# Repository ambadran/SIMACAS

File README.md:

# SIMACAS - Smart Intillegent Monitoring and Control Agriculture System

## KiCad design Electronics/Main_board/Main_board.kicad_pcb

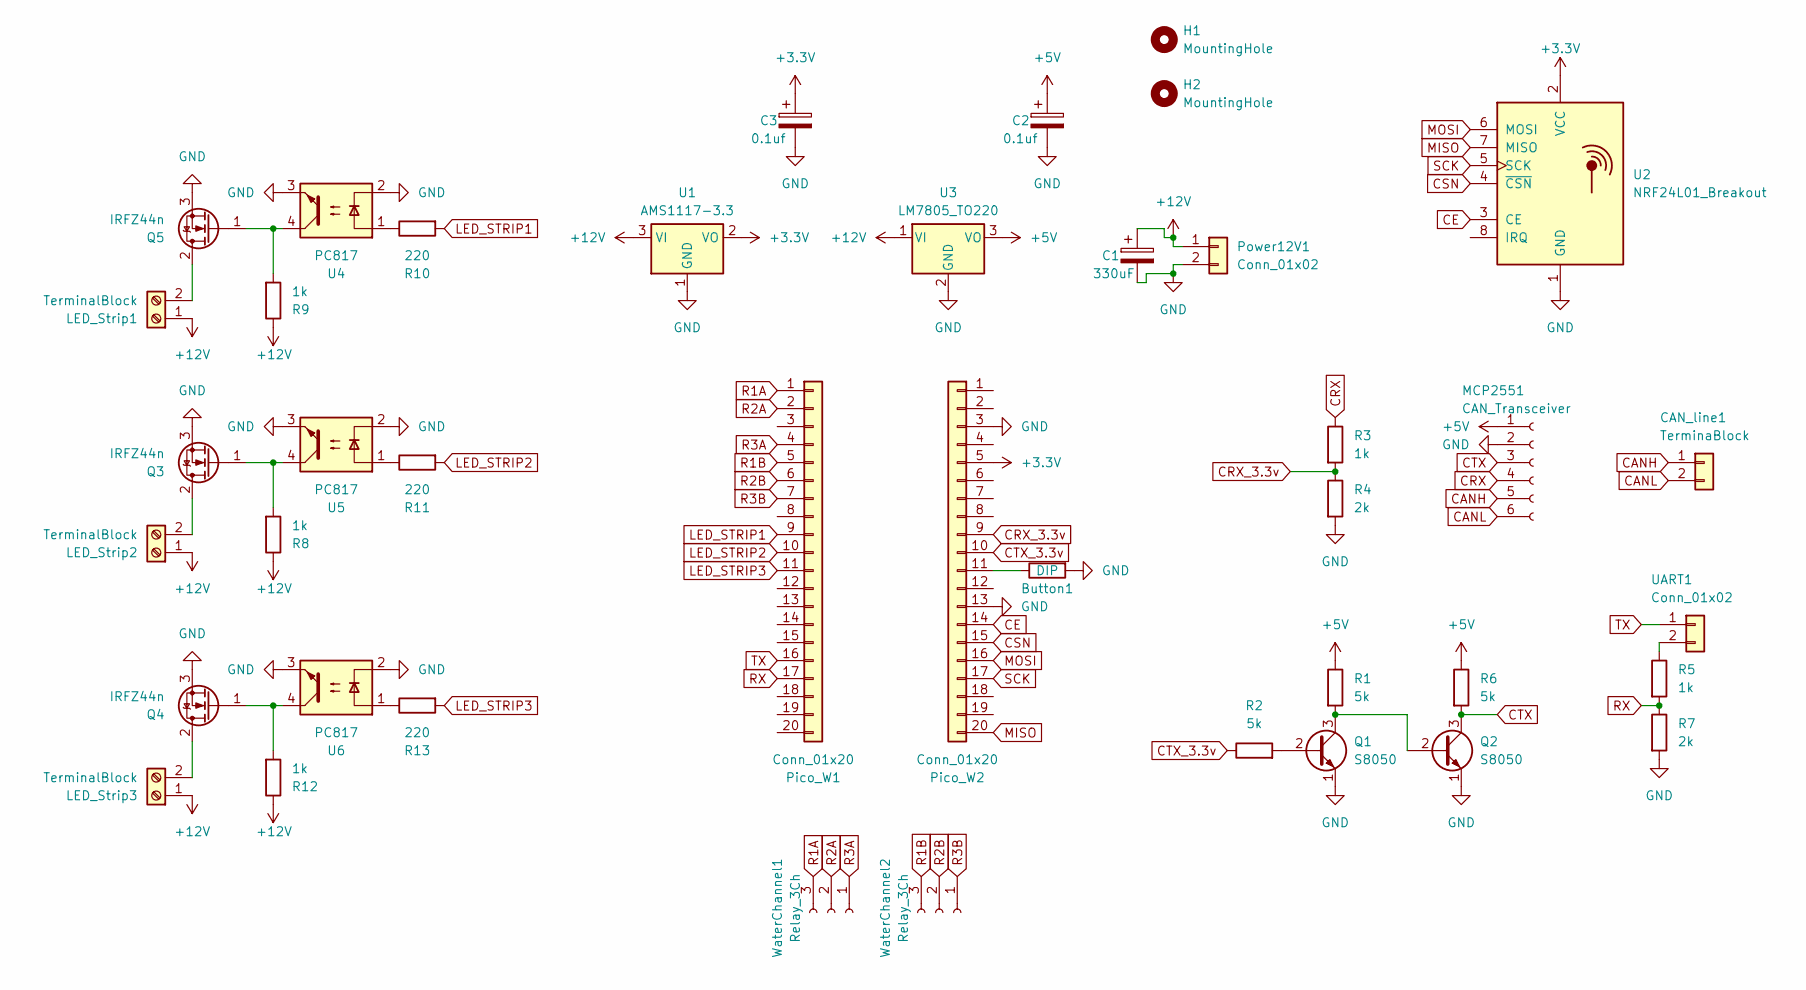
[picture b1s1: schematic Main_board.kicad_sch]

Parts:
Button1: DIP; R_Axial_DIN0207_L6.3mm_D2.5mm_P5.08mm_Vertical
C1: 330uF; CP_Radial_D8.0mm_P3.80mm
C2, C3: 0.1uf; CP_Radial_D4.0mm_P2.00mm
CAN_line1: TerminaBlock; TerminalBlock_bornier-2_P5.08mm
H1, H2: MountingHole; MountingHole_3.2mm_M3_DIN965_Pad_TopBottom
LED_Strip1, LED_Strip2, LED_Strip3: TerminalBlock; TerminalBlock_bornier-2_P5.08mm
MCP2551: CAN_Transceiver; PinSocket_1x06_P2.54mm_Vertical
Pico_W1, Pico_W2: Conn_01x20; PinSocket_1x20_P2.54mm_Vertical
Power12V1: Conn_01x02; JST_EH_B2B-EH-A_1x02_P2.50mm_Vertical
Q1, Q2: S8050; TO-92_Inline_Wide
Q3, Q4, Q5: IRFZ44n; TO-220-3_Vertical
R1, R2, R6: 5k; R_Axial_DIN0207_L6.3mm_D2.5mm_P7.62mm_Horizontal
R3, R5, R8, R9, R12: 1k; R_Axial_DIN0207_L6.3mm_D2.5mm_P7.62mm_Horizontal
R4, R7: 2k; R_Axial_DIN0207_L6.3mm_D2.5mm_P7.62mm_Horizontal
R10, R11, R13: 220; R_Axial_DIN0207_L6.3mm_D2.5mm_P7.62mm_Horizontal
U1: AMS1117-3.3; TO-220-3_Vertical
U2: NRF24L01_Breakout; nRF24L01_Breakout
U3: LM7805_TO220; TO-220-3_Vertical
U4, U5, U6: PC817; DIP-4_W7.62mm
UART1: Conn_01x02; JST_EH_B2B-EH-A_1x02_P2.50mm_Vertical
WaterChannel1, WaterChannel2: Relay_3Ch; JST_EH_B3B-EH-A_1x03_P2.50mm_Vertical

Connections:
+3.3V: C3.1, Pico_W2.5, U1.2 (VO), U2.2 (VCC)
+5V: C2.1, MCP2551.1, R1.1, R6.1, U3.3 (VO)
+12V: C1.1, LED_Strip1.1, LED_Strip2.1, LED_Strip3.1, Power12V1.1, R8.1, R9.1, R12.1, U1.3 (VI), U3.1 (VI)
CANH: CAN_line1.1, MCP2551.5
CANL: CAN_line1.2, MCP2551.6
CE: Pico_W2.14, U2.3 (CE)
CRX: MCP2551.4, R3.1
CRX_3.3v: Pico_W2.9, R3.2, R4.1
CSN: Pico_W2.15, U2.4 (~CSN)
CTX: MCP2551.3, Q2.3 (C), R6.2
CTX_3.3v: Pico_W2.10, R2.1
GND: Button1.2, C1.2, C2.2, C3.2, MCP2551.2, Pico_W2.3, Pico_W2.13, Power12V1.2, Q1.1 (E), Q2.1 (E), Q3.3 (S), Q4.3 (S), Q5.3 (S), R4.2, R7.2, U1.1 (GND), U2.1 (GND), U3.2 (GND), U4.2, U4.3, U5.2, U5.3, U6.2, U6.3
LED_STRIP1: Pico_W1.9, R10.2
LED_STRIP2: Pico_W1.10, R11.2
LED_STRIP3: Pico_W1.11, R13.2
MISO: Pico_W2.20, U2.7 (MISO)
MOSI: Pico_W2.16, U2.6 (MOSI)
unnamed: LED_Strip1.2, Q5.2 (D)
unnamed: LED_Strip2.2, Q3.2 (D)
unnamed: LED_Strip3.2, Q4.2 (D)
unnamed: Button1.1, Pico_W2.11
unnamed: Q1.2 (B), R2.2
unnamed: Q1.3 (C), Q2.2 (B), R1.2
unnamed: Q3.1 (G), R8.2, U5.4
unnamed: Q4.1 (G), R12.2, U6.4
unnamed: Q5.1 (G), R9.2, U4.4
unnamed: R10.1, U4.1
unnamed: R11.1, U5.1
unnamed: R13.1, U6.1
unnamed: R5.1, UART1.2
R1A: Pico_W1.1, WaterChannel1.3
R1B: Pico_W1.5, WaterChannel2.3
R2A: Pico_W1.2, WaterChannel1.2
R2B: Pico_W1.6, WaterChannel2.2
R3A: Pico_W1.4, WaterChannel1.1
R3B: Pico_W1.7, WaterChannel2.1
RX: Pico_W1.17, R5.2, R7.1
SCK: Pico_W2.17, U2.5 (SCK)
TX: Pico_W1.16, UART1.1

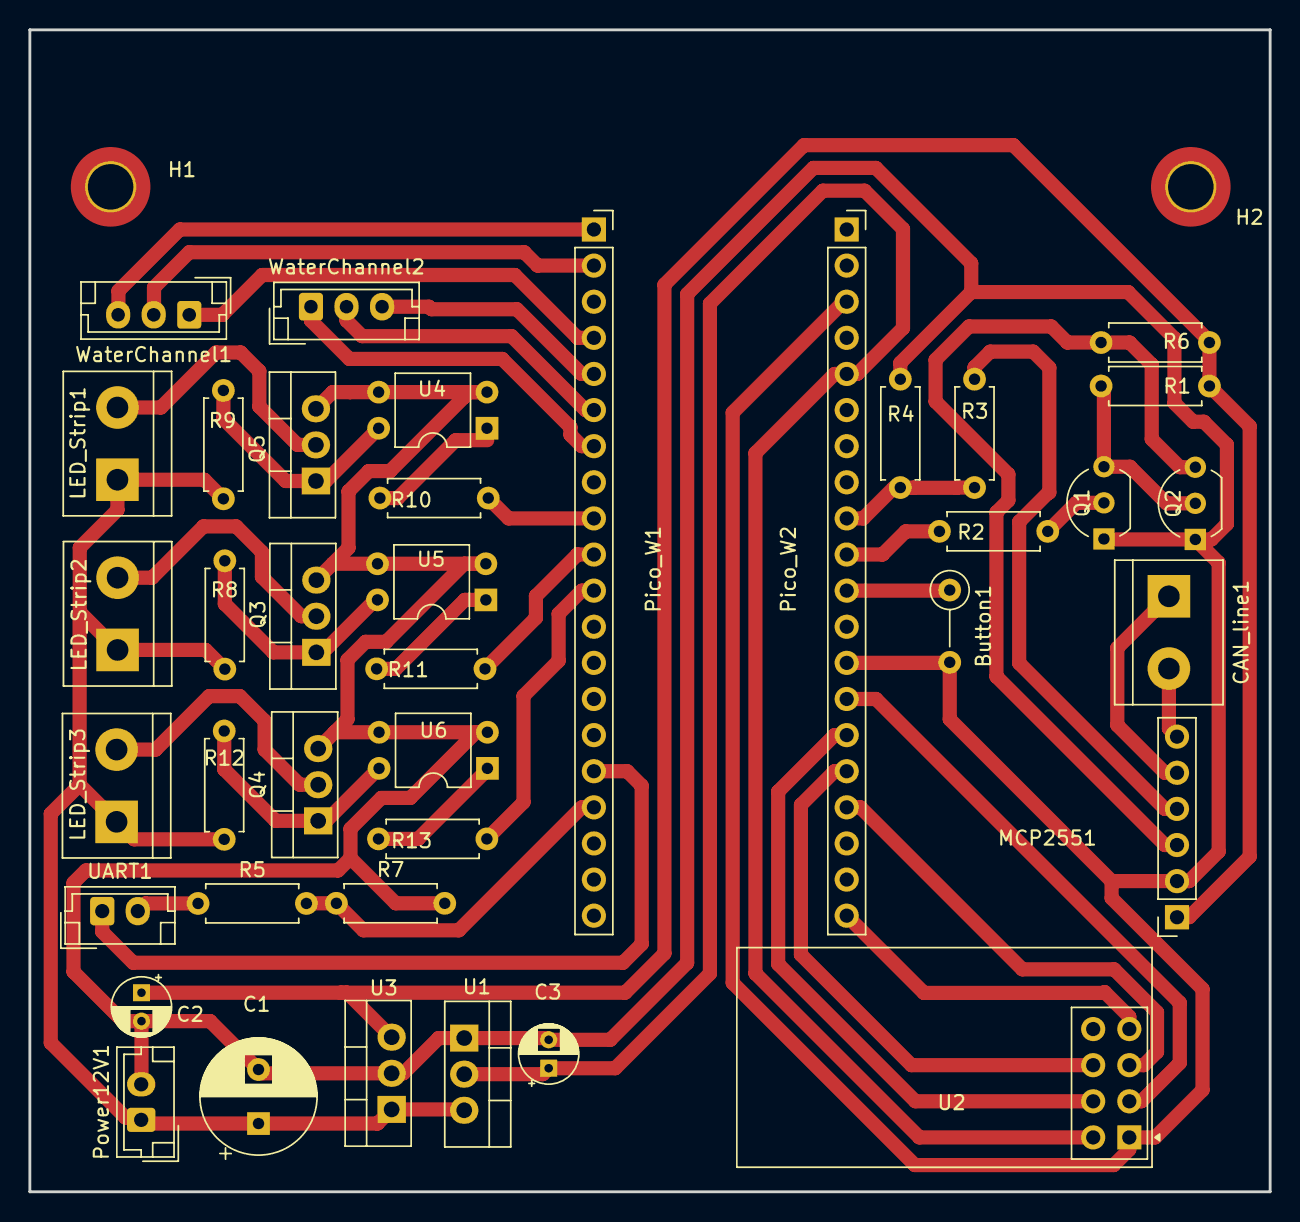
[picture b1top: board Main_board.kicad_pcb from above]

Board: 2 copper layers, 87.2 x 81.7 mm, 41 parts (0 on the bottom side), 39 nets.

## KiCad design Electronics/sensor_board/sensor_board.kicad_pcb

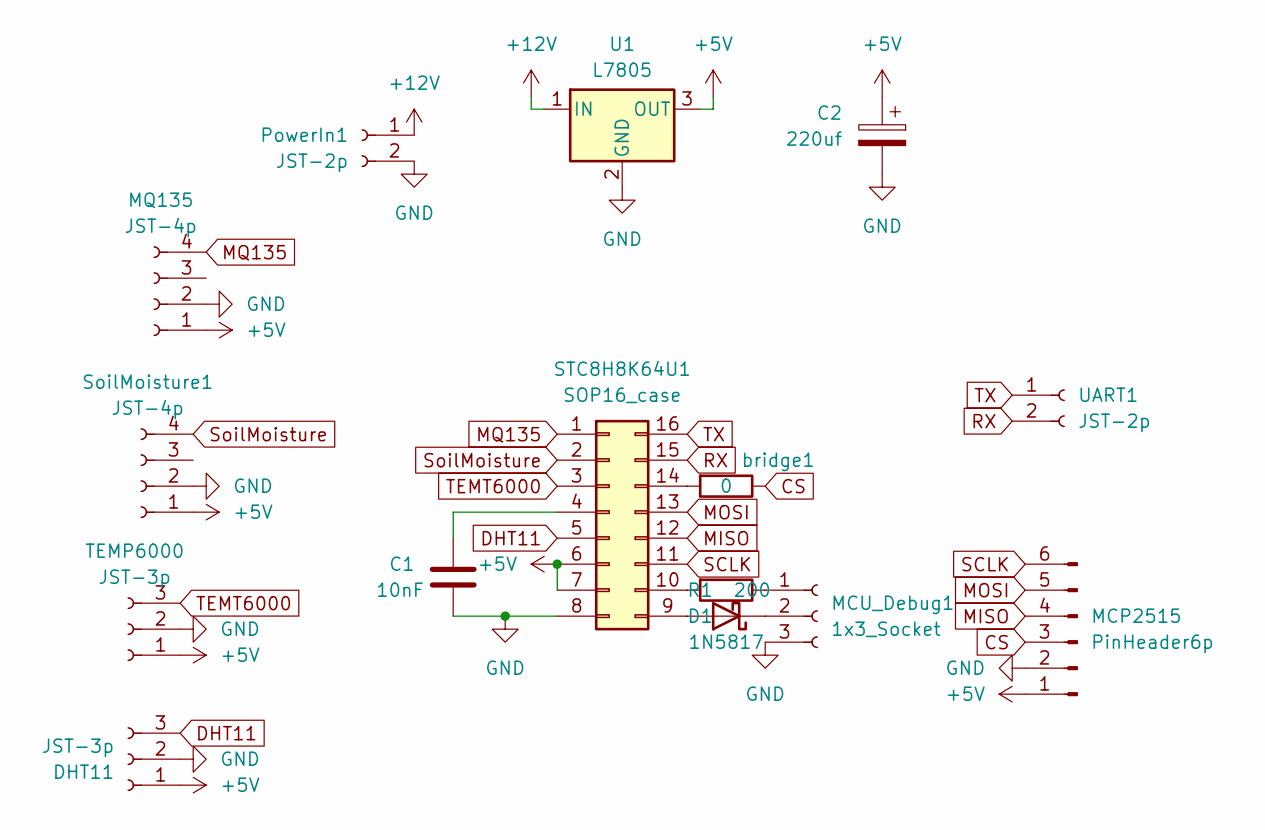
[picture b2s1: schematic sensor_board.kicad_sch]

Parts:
C1: 10nF; C_Disc_D5.0mm_W2.5mm_P5.00mm
C2: 220uf; CP_Radial_D6.3mm_P2.50mm
D1: 1N5817; D_DO-41_SOD81_P10.16mm_Horizontal
DHT11: JST-3p; JST_EH_B3B-EH-A_1x03_P2.50mm_Vertical
MCP2515: PinHeader6p; PinSocket_1x06_P2.54mm_Vertical
MCU_Debug1: 1x3_Socket; PinSocket_1x03_P2.54mm_Vertical
MQ135: JST-4p; JST_EH_B4B-EH-A_1x04_P2.50mm_Vertical
PowerIn1: JST-2p; JST_EH_B2B-EH-A_1x02_P2.50mm_Vertical
R1: 200; R_Axial_DIN0207_L6.3mm_D2.5mm_P7.62mm_Horizontal
STC8H8K64U1: SOP16_case; DIP-16_W7.62mm_LongPads
SoilMoisture1: JST-4p; JST_EH_B4B-EH-A_1x04_P2.50mm_Vertical
TEMP6000: JST-3p; JST_EH_B3B-EH-A_1x03_P2.50mm_Vertical
U1: L7805; TO-220-3_Vertical
UART1: JST-2p; JST_EH_B2B-EH-A_1x02_P2.50mm_Vertical
bridge1: 0; R_Axial_DIN0207_L6.3mm_D2.5mm_P7.62mm_Horizontal

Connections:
+5V: C2.1, DHT11.1, MCP2515.1, MQ135.1, STC8H8K64U1.6, STC8H8K64U1.7, SoilMoisture1.1, TEMP6000.1, U1.3 (OUT)
+12V: PowerIn1.1, U1.1 (IN)
CS: MCP2515.3, bridge1.1
DHT11: DHT11.3, STC8H8K64U1.5
GND: C1.2, C2.2, DHT11.2, MCP2515.2, MCU_Debug1.3, MQ135.2, PowerIn1.2, STC8H8K64U1.8, SoilMoisture1.2, TEMP6000.2, U1.2 (GND)
MISO: MCP2515.4, STC8H8K64U1.12
MOSI: MCP2515.5, STC8H8K64U1.13
MQ135: MQ135.4, STC8H8K64U1.1
unnamed: D1.2 (A), STC8H8K64U1.9
unnamed: D1.1 (K), MCU_Debug1.2
unnamed: MCU_Debug1.1, R1.1
unnamed: C1.1, STC8H8K64U1.4
unnamed: R1.2, STC8H8K64U1.10
unnamed: STC8H8K64U1.14, bridge1.2
RX: STC8H8K64U1.15, UART1.2
SCLK: MCP2515.6, STC8H8K64U1.11
SoilMoisture: STC8H8K64U1.2, SoilMoisture1.4
TEMT6000: STC8H8K64U1.3, TEMP6000.3
TX: STC8H8K64U1.16, UART1.1

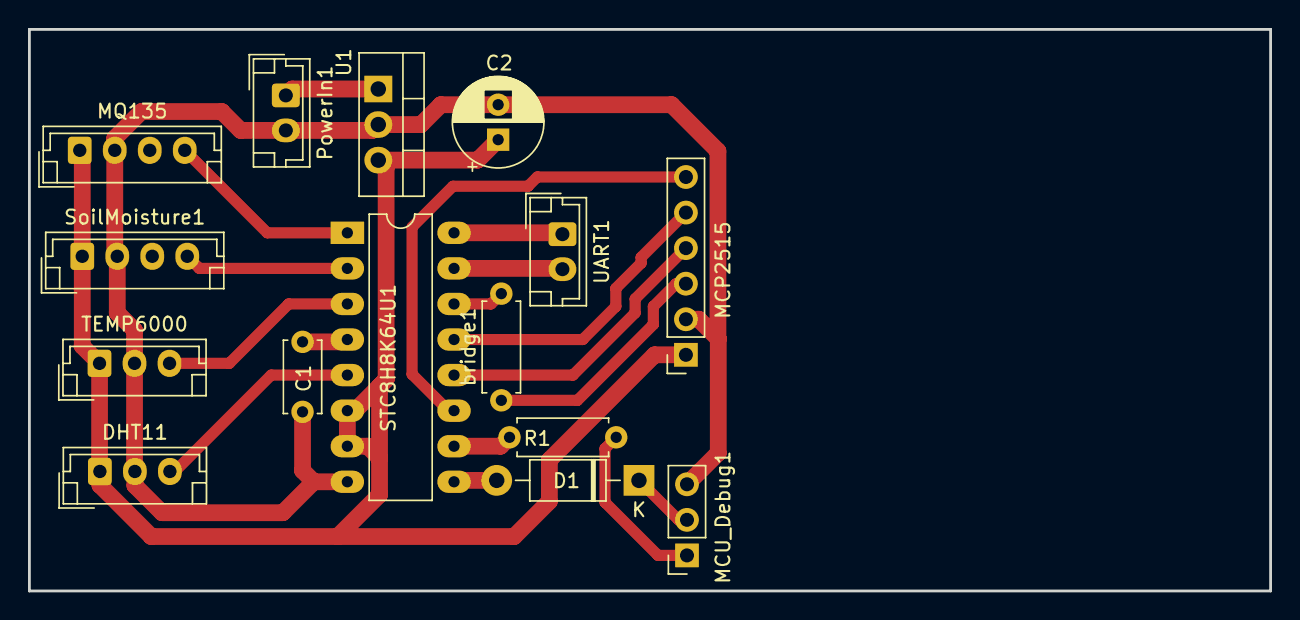
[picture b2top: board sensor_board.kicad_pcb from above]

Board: 2 copper layers, 88.6 x 40.1 mm, 15 parts (0 on the bottom side), 19 nets.

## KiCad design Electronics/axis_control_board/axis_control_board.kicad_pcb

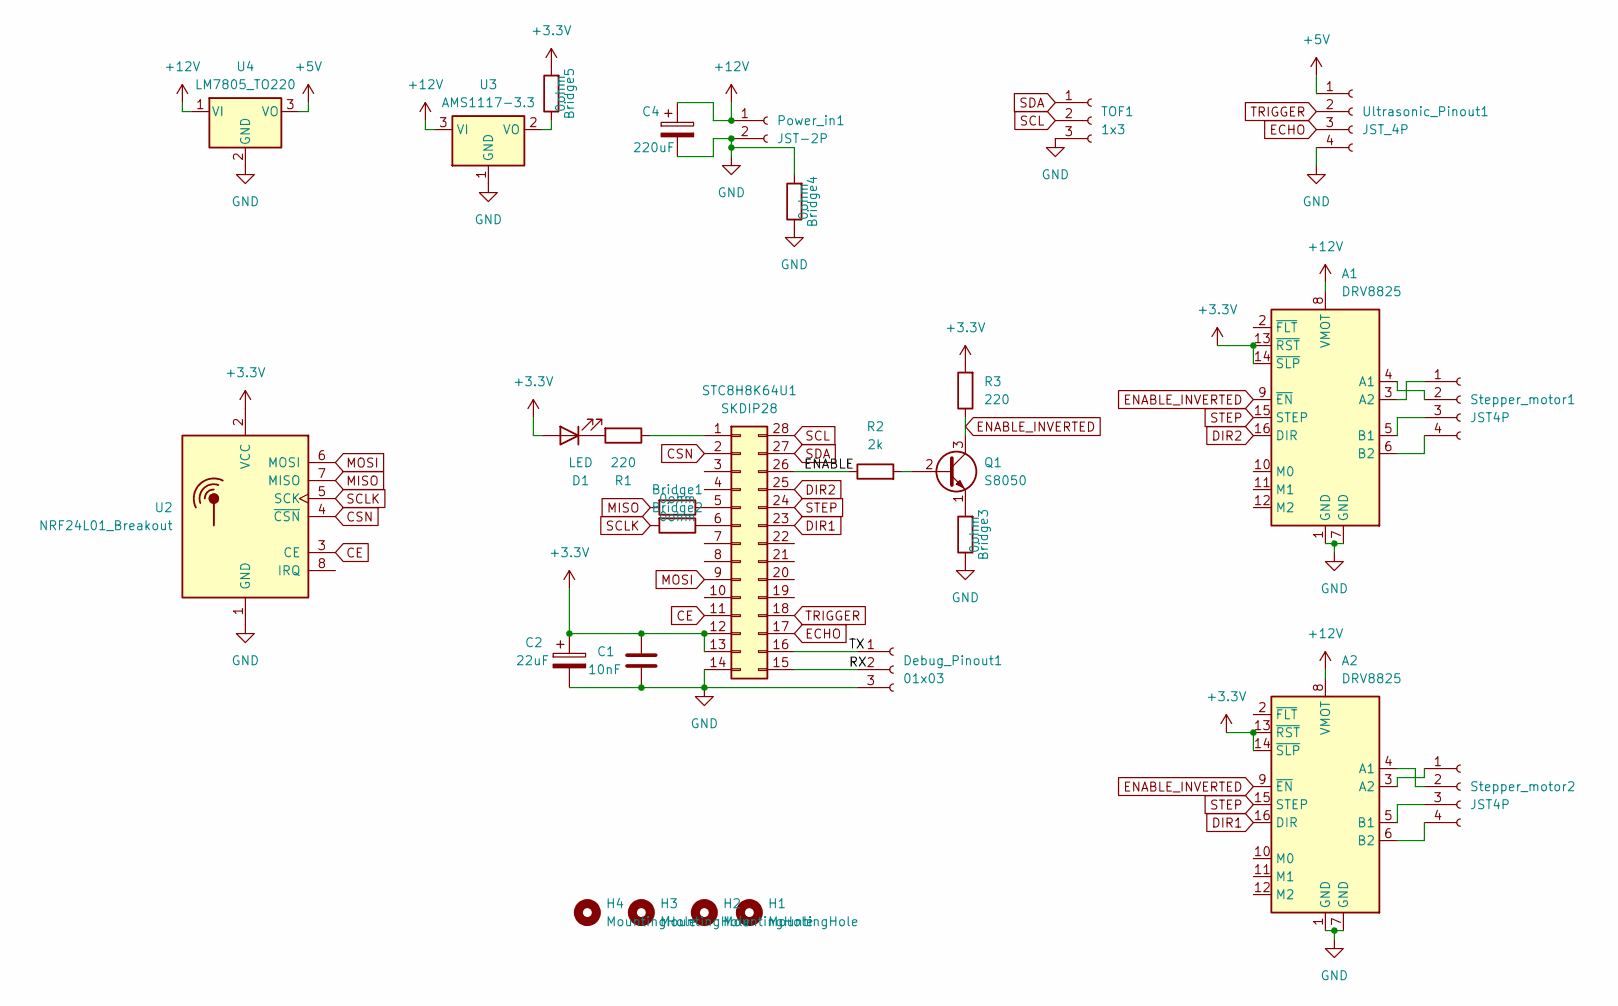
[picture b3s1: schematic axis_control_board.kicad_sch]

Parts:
A1, A2: DRV8825; Pololu_Breakout-16_15.2x20.3mm
Bridge1, Bridge2, Bridge3, Bridge4: 0ohm; R_Axial_DIN0207_L6.3mm_D2.5mm_P7.62mm_Horizontal
Bridge5: 0ohm; R_Axial_DIN0207_L6.3mm_D2.5mm_P5.08mm_Vertical
C1: 10nF; C_Disc_D5.0mm_W2.5mm_P2.50mm
C2: 22uF; CP_Radial_D5.0mm_P2.00mm
C4: 220uF; CP_Radial_D5.0mm_P2.50mm
D1: LED; LED_D3.0mm
Debug_Pinout1: 01x03; PinSocket_1x03_P2.54mm_Vertical
H1, H2, H3, H4: MountingHole; MountingHole_3.2mm_M3_Pad_TopOnly
Power_in1: JST-2P; JST_EH_B2B-EH-A_1x02_P2.50mm_Vertical
Q1: S8050; TO-92_Inline
R1, R3: 220; R_Axial_DIN0207_L6.3mm_D2.5mm_P7.62mm_Horizontal
R2: 2k; R_Axial_DIN0207_L6.3mm_D2.5mm_P7.62mm_Horizontal
STC8H8K64U1: SKDIP28; DIP-28_W7.62mm_LongPads
Stepper_motor1, Stepper_motor2: JST4P; JST_EH_B4B-EH-A_1x04_P2.50mm_Vertical
TOF1: 1x3; PinSocket_1x03_P2.54mm_Vertical
U2: NRF24L01_Breakout; nRF24L01_Breakout
U3: AMS1117-3.3; TO-220-3_Vertical
U4: LM7805_TO220; TO-220-3_Vertical
Ultrasonic_Pinout1: JST_4P; JST_EH_B4B-EH-A_1x04_P2.50mm_Vertical

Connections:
+3.3V: A1.13 (~RST), A1.14 (~SLP), A2.13 (~RST), A2.14 (~SLP), Bridge5.2, C1.2, C2.1, D1.2 (A), R3.2, STC8H8K64U1.12, STC8H8K64U1.13, U2.2 (VCC)
+5V: U4.3 (VO), Ultrasonic_Pinout1.1
+12V: A1.8 (VMOT), A2.8 (VMOT), C4.1, Power_in1.1, U3.3 (VI), U4.1 (VI)
/ENABLE: R2.1, STC8H8K64U1.26
/RX: Debug_Pinout1.2, STC8H8K64U1.15
/TX: Debug_Pinout1.1, STC8H8K64U1.16
CE: STC8H8K64U1.11, U2.3 (CE)
CSN: STC8H8K64U1.2, U2.4 (~CSN)
DIR1: A2.16 (DIR), STC8H8K64U1.23
DIR2: A1.16 (DIR), STC8H8K64U1.25
ECHO: STC8H8K64U1.17, Ultrasonic_Pinout1.3
ENABLE_INVERTED: A1.9 (~EN), A2.9 (~EN), Q1.3 (C), R3.1
GND: A1.1 (GND), A1.7 (GND), A2.1 (GND), A2.7 (GND), Bridge3.1, Bridge4.1, Bridge4.2, C1.1, C2.2, C4.2, Debug_Pinout1.3, Power_in1.2, STC8H8K64U1.14, TOF1.3, U2.1 (GND), U3.1 (GND), U4.2 (GND), Ultrasonic_Pinout1.4
MISO: Bridge1.2, U2.7 (MISO)
MOSI: STC8H8K64U1.9, U2.6 (MOSI)
unnamed: A1.4 (A1), Stepper_motor1.2
unnamed: A1.3 (A2), Stepper_motor1.1
unnamed: A1.5 (B1), Stepper_motor1.3
unnamed: A1.6 (B2), Stepper_motor1.4
unnamed: A2.4 (A1), Stepper_motor2.2
unnamed: A2.3 (A2), Stepper_motor2.1
unnamed: A2.5 (B1), Stepper_motor2.3
unnamed: A2.6 (B2), Stepper_motor2.4
unnamed: D1.1 (K), R1.2
unnamed: Q1.2 (B), R2.2
unnamed: Bridge3.2, Q1.1 (E)
unnamed: R1.1, STC8H8K64U1.1
unnamed: Bridge1.1, STC8H8K64U1.5
unnamed: Bridge2.1, STC8H8K64U1.6
unnamed: Bridge5.1, U3.2 (VO)
SCL: STC8H8K64U1.28, TOF1.2
SCLK: Bridge2.2, U2.5 (SCK)
SDA: STC8H8K64U1.27, TOF1.1
STEP: A1.15 (STEP), A2.15 (STEP), STC8H8K64U1.24
TRIGGER: STC8H8K64U1.18, Ultrasonic_Pinout1.2

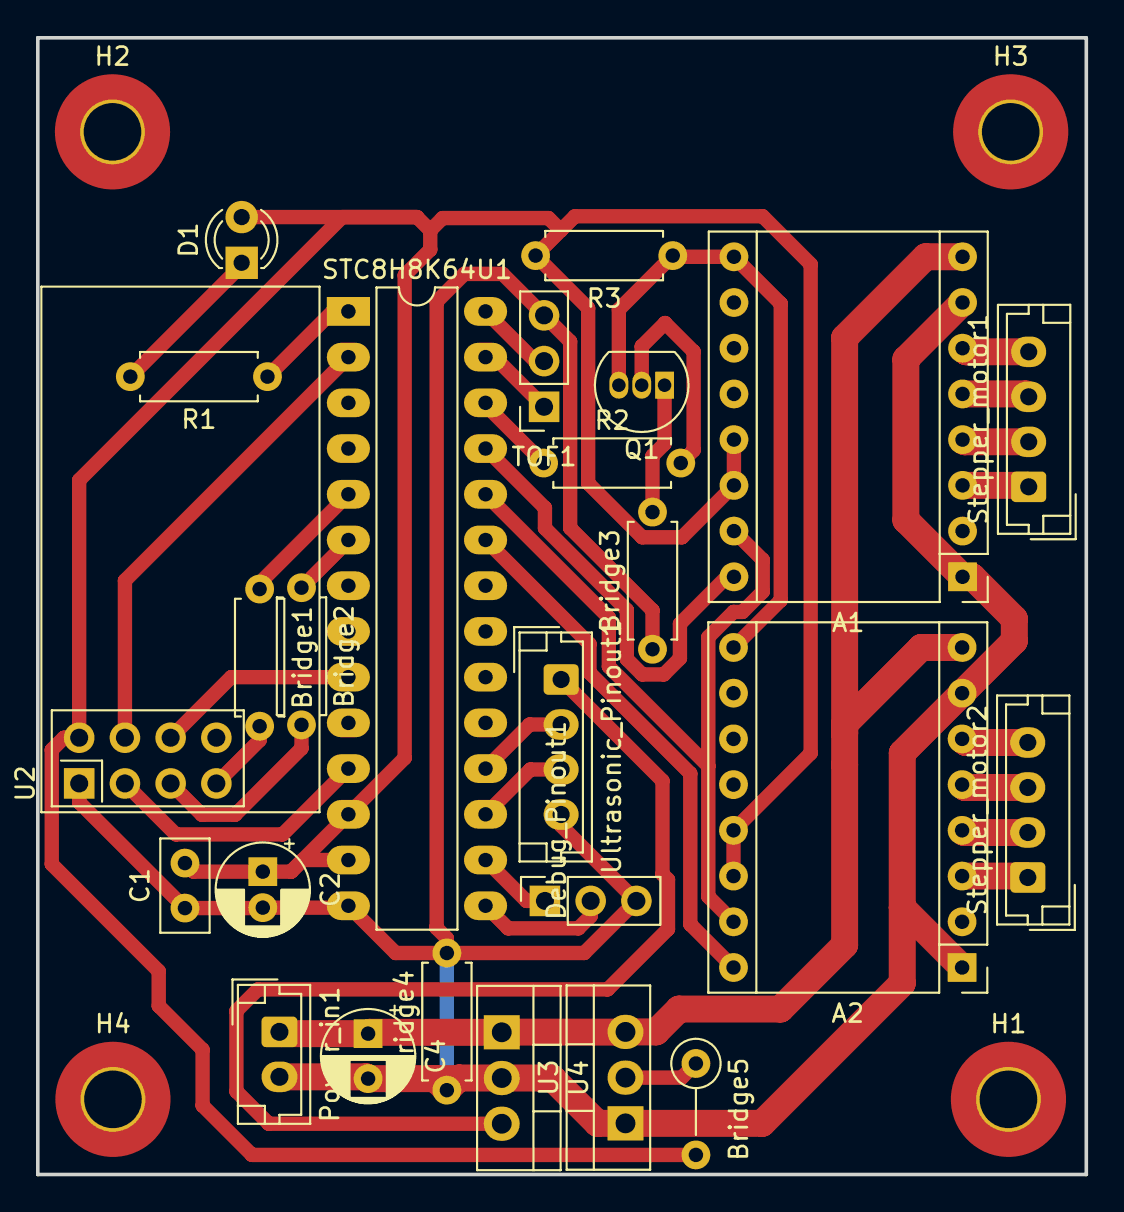
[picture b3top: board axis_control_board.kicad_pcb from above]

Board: 2 copper layers, 58.2 x 63.2 mm, 29 parts (0 on the bottom side), 35 nets.

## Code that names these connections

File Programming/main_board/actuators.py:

'''
Abstraction to control ALL Actuators together
    - Axis Control Movements
    - Water Distribution Relay States
    - LED Strip PWM signal
'''
from axis_control import AxisControl
from water_distribution import WaterDistribution
from led_strip import LedStrip

class Actuators:
    '''
    Abstraction to control ALL Actuators together
        - Axis Control Movements
        - Water Distribution Relay States
        - LED Strip PWM signal
    '''
    SCK_PIN = const(18)
    MOSI_PIN = const(19)
    MISO_PIN = const(16)
    CSN_PIN = const(20)
    CE_PIN = const(21)

    RELAY1A_PIN = const(0)
    RELAY2A_PIN = const(1)
    RELAY3A_PIN = const(2)
    RELAY1B_PIN = const(3)
    RELAY2B_PIN = const(4)
    RELAY3B_PIN = const(5)

    LED_STRIP1_PIN = const(7)
    LED_STRIP2_PIN = const(8)
    LED_STRIP3_PIN = const(9)

    def __init__(self):
        # 1- Axis Control of Movements through nRF24l01
        self.axis = AxisControl(Actuators.SCK_PIN, Actuators.MOSI_PIN, Actuators.MISO_PIN,
                                Actuators.CSN_PIN, Actuators.CE_PIN)

        # Solenoid Valve water/fertilizer channels controlled by Relays
        self.distribution0 = WaterDistribution(Actuators.RELAY1A_PIN,
                                               Actuators.RELAY2A_PIN, 
                                               Actuators.RELAY3A_PIN)
        self.distribution1 = WaterDistribution(Actuators.RELAY1B_PIN, 
                                               Actuators.RELAY2B_PIN, 
                                               Actuators.RELAY3B_PIN)
        self.distributions = (self.distribution0, self.distribution1)

        # LED Strips
        self.led_strip0 = LedStrip(self.LED_STRIP1_PIN)
        self.led_strip1 = LedStrip(self.LED_STRIP2_PIN)
        self.led_strip2 = LedStrip(self.LED_STRIP3_PIN)
        self.led_strips = (self.led_strip0, self.led_strip1, self.led_strip2)

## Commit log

2024-04-08 added axis_control circuit and programming files
2024-04-08 Further development in terminal protocol fo STC MCU
2024-04-12 finished terminal component and stepper_motor component :D
2024-04-13 Now I call move_abs(distance) from upy and the steppers move through stc ;)
2024-04-13 added .shapr and .step file
2024-04-13 started developing ultrasonic drivers
2024-04-14 further dev in ultrasonic module
2024-04-14 finallized state machine design for ultrasonic sensor
2024-04-15 developing state machine algorithm for ultrasonic
2024-04-15 added BOM files
2024-04-15 finished ultrasonic phase and status state machines c development with successful compilation, pending actual testing ;p
2024-04-15 added water pump pwm controller circuit
2024-04-16 added ultrasonic terminal commands
2024-04-16 hit a brick wall, MCU doesn't do anything, maybe stack overflow problem?!
2024-04-20 further development in axis control board
2024-04-20 minor changes
2024-04-20 finished axis control PCB design
2024-04-21 added Gerber and Gcode files for axis control PCB
2024-04-21 added BOMs and more gcode files
2024-04-23 minor changes for axis control PCB
2024-05-11 updated axis_control PCB and fixed hardware bug
2024-05-11 started thesis and exported new axis pdfs
2024-05-13 minor deployment changes
2024-05-14 further development in thesis
2024-05-16 finished almost all intro and literature review
2024-05-23 started web development for pico w
2024-05-23 website developed and functional, pending water irrigation buttons
2024-06-03 minor changes in web development and thesis
2024-06-03 finished methodology without screenshots or photos
2024-06-08 modified BOMs and created sensor_board electronics and programming files. Plus some file rearrangement
2024-06-09 minor changes to thesis
2024-06-13 further development in sensor board
2024-06-13 finished sensor board PCB
2024-06-14 finished implementing full terminal on sensor board :D
2024-06-14 finished all sensor_board code (except DHT11 bug and CAN module)
2024-06-15 added some STLs
2024-06-17 finished second wide sprinkler
2024-06-18 finished electronics side axis frame and battery holder
2024-06-21 Main MCU now communicate with multiple nRF. Added Main Board Schematic
2024-06-21 Main Board Code re-written; finished actuators, html pages and started server-side handling
2024-06-22 Finished linking web app with Actuators ;)
2024-06-22 added Syncronized Movement for axis when MPC is enabled
2024-06-23 finished Main Board PCB
2024-06-23 added finished thesis and media folder
2024-06-23 added Main Board PDFs
2024-06-23 updated table of content and table of figures in thesis
2024-06-23 added Final .step & .shapr files for WHOLE Project
2024-06-23 added sensors.py
2024-06-24 Major Bug Fixes in Main Board
2024-06-25 added BOM
2024-06-25 finished BOM
2024-06-25 modified BOM
